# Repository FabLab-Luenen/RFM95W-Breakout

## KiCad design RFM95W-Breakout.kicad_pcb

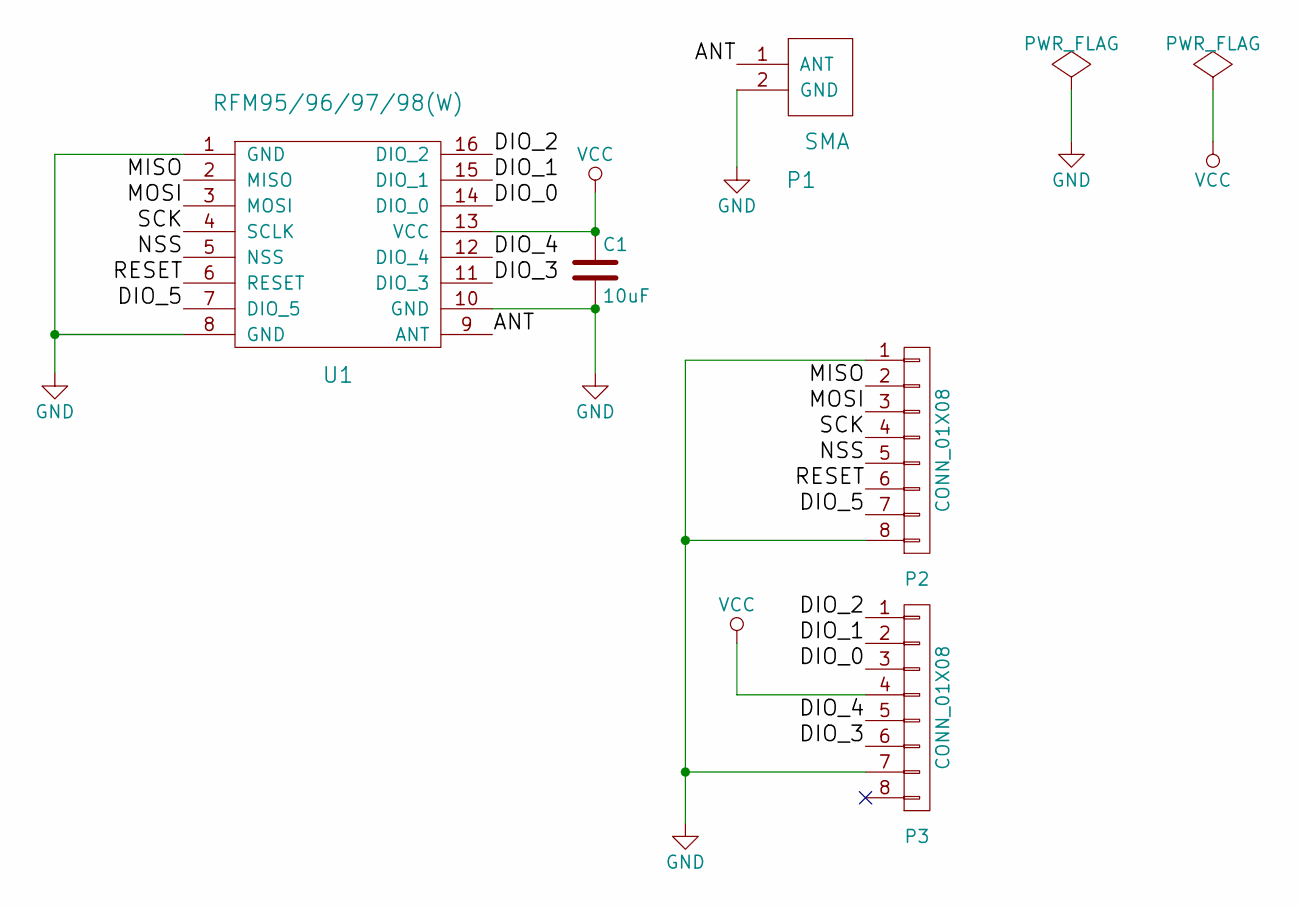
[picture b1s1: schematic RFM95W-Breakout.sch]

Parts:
C1: 10uF; C_0805
P1: SMA; SMA_THT_Jack_Straight
P2, P3: CONN_01X08; Pin_Header_Straight_1x08
U1: RFM95/96/97/98(W); RFM95(W)

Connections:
/ANT: P1.1 (ANT), U1.9 (ANT)
/DIO_0: P3.3, U1.14 (DIO_0)
/DIO_1: P3.2, U1.15 (DIO_1)
/DIO_2: P3.1, U1.16 (DIO_2)
/DIO_3: P3.6, U1.11 (DIO_3)
/DIO_4: P3.5, U1.12 (DIO_4)
/DIO_5: P2.7, U1.7 (DIO_5)
/MISO: P2.2, U1.2 (MISO)
/MOSI: P2.3, U1.3 (MOSI)
/NSS: P2.5, U1.5 (NSS)
/RESET: P2.6, U1.6 (RESET)
/SCK: P2.4, U1.4 (SCLK)
GND: C1.2, P1.2 (GND), P2.1, P2.8, P3.7, U1.1 (GND), U1.8 (GND), U1.10 (GND)
VCC: C1.1, P3.4, U1.13 (VCC)

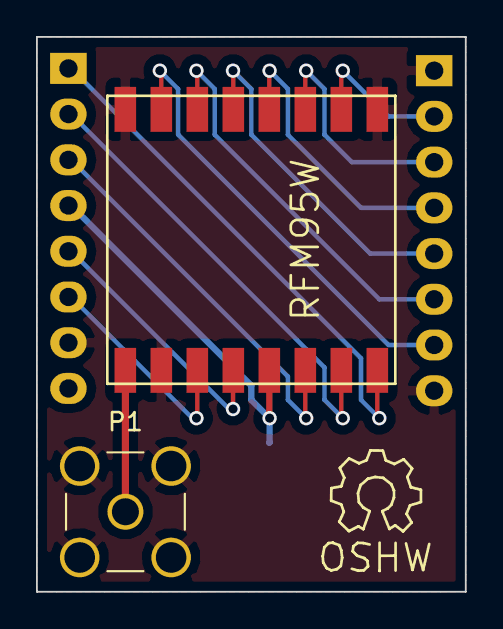
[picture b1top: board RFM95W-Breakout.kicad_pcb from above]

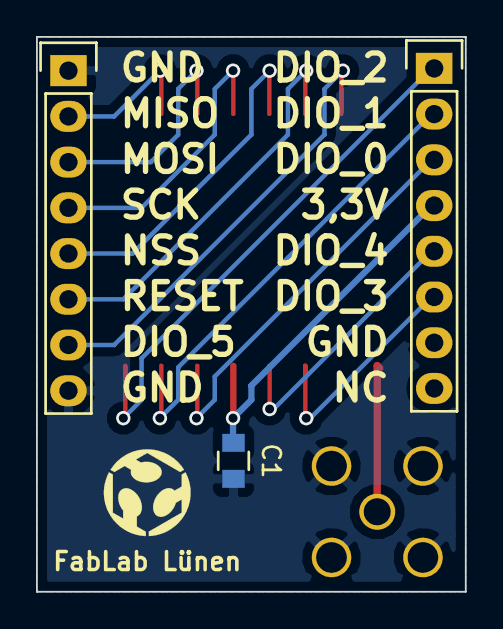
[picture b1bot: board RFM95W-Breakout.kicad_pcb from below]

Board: 2 copper layers, 23.8 x 30.8 mm, 5 parts (3 on the bottom side), 14 nets.

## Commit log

2017-03-26 deleted few backup files
